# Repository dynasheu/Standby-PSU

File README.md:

# Standby-PSU
Small sandby PSU for low power applications.

## standby-psu-test
This sketch is for debugging and testing on arduino. Uses normal IRremote.h library.

## standby-psu-master
This sketch is for use with ATTiny.
Uses tiny_IRremote.h and SendOnlySoftwareSerial.h libraries.

I/O:
- button
- led
- relay
- ir
- serial out

PCB and components coming soon

## standby-psu-slave
Comming soon.

This sketch is for use with ATTiny.
Uses ReceiveOnlySoftwareSerial.h library.

I/O:
- button
- led
- relay
- mute relay
- serial in

Same PCB as master.

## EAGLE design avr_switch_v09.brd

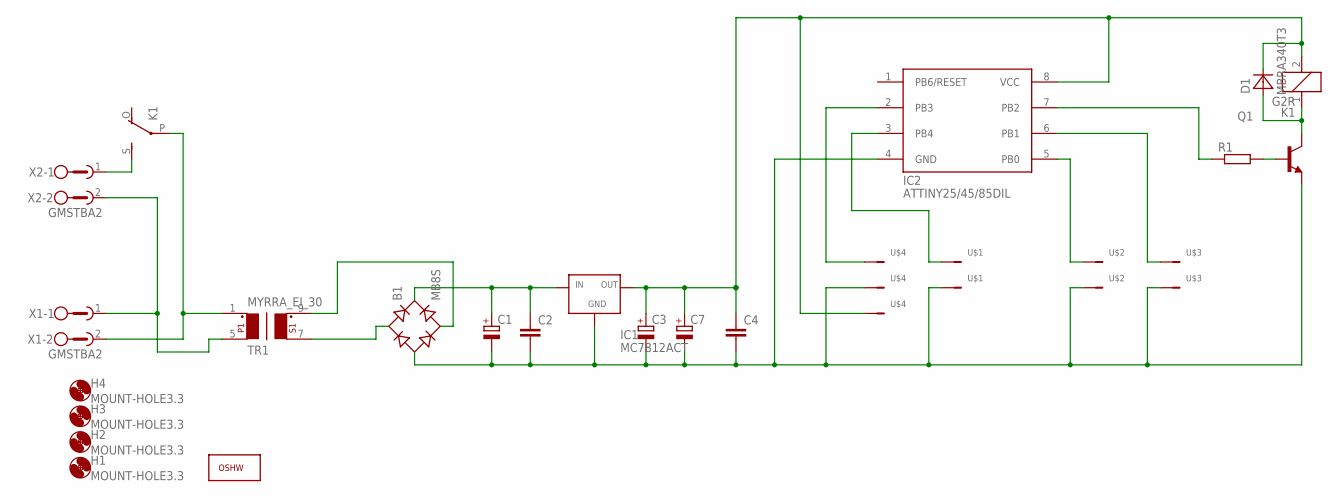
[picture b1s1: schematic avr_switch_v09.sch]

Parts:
B1: MB8S; SOIC-4
C1: CPOL-EUE5-10.5; E5-10,5
C2, C4: C-EUC0805; C0805
C3: CPOL-EUCT6032; CT6032
C7: CPOL-EUD/7343-31W; D/7343-31W
D1: MBRA340T3; SMA
H1, H2, H3, H4: MOUNT-HOLE3.3; 3,3
IC1: MC7812ACT; TO220V
IC2: ATTINY25/45/85DIL; DIL08
K1: G2R
Q1: BC548-NPN-TO92-CBE; TO92-CBE
R1: R-EU_R1206; R1206
TR1: MYRRA_EI_30; MYRRA-EI30
U$1, U$2, U$3: MOLEX-VERT-KK-2-; MOLEX-KK-VERT-2PIN
U$4: MOLEX-VERT-KK-3-3PIN; MOLEX-KK-VERT-3PIN
U$5: OSHWOSHW_TOP; OSHW_F
X1, X2: GMSTBA2

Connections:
GND: B1.-, C1.-, C2.2, C3.-, C4.2, C7.-, IC1.2 (GND), IC2.4 (GND), Q1.E, U$1.1, U$2.1, U$3.1, U$4.2
unnamed: IC2.7 (PB2), R1.1
unnamed: B1.~1 (AC1), TR1.7
unnamed: B1.~2 (AC2), TR1.9
unnamed: IC2.3 (PB4), U$1.2
unnamed: IC2.5 (PB0), U$2.2
unnamed: IC2.6 (PB1), U$3.2
unnamed: Q1.B, R1.2
unnamed: K1.S, X2.1
unnamed: B1.+, C1.+, C2.1, IC1.1 (IN)
unnamed: TR1.5, X1.1, X2.2
unnamed: K1.P, TR1.1, X1.2
unnamed: IC2.2 (PB3), U$4.3
RELN: D1.A, K1.1, Q1.C
VCC: C3.+, C4.1, C7.+, D1.C, IC1.3 (OUT), IC2.8 (VCC), K1.2, U$4.1

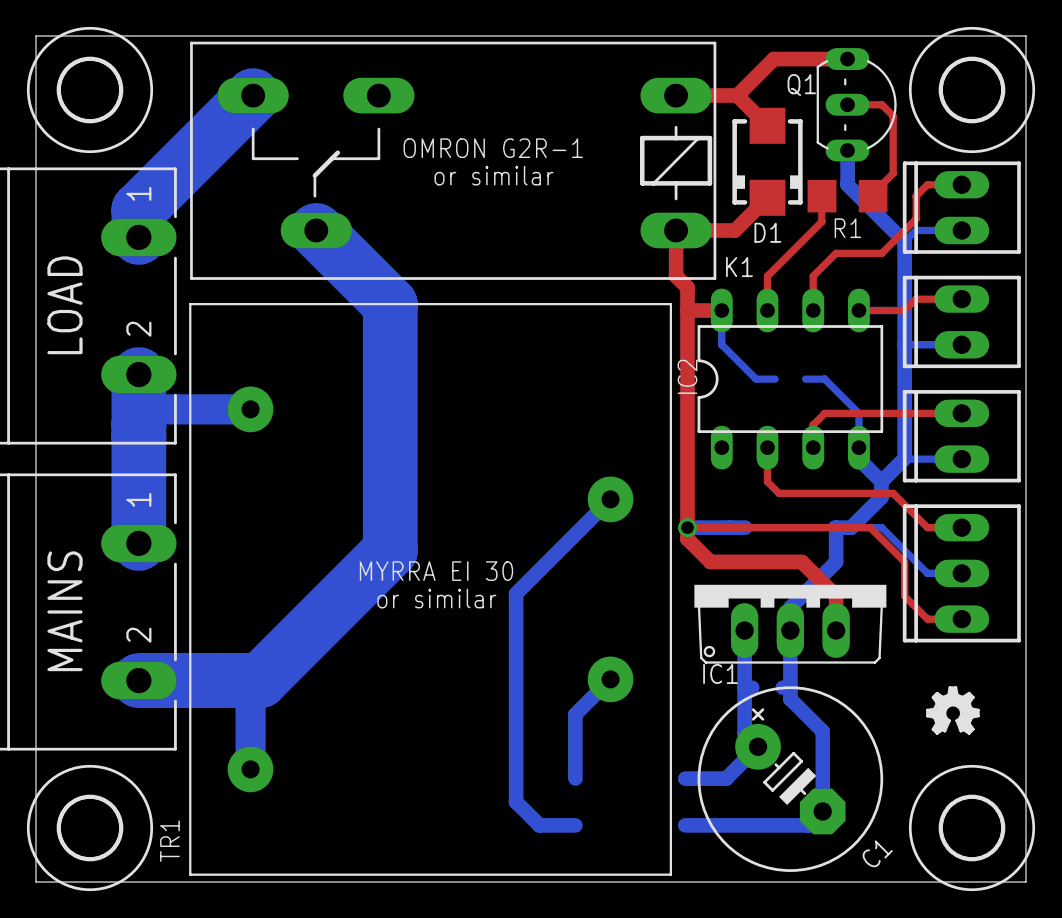
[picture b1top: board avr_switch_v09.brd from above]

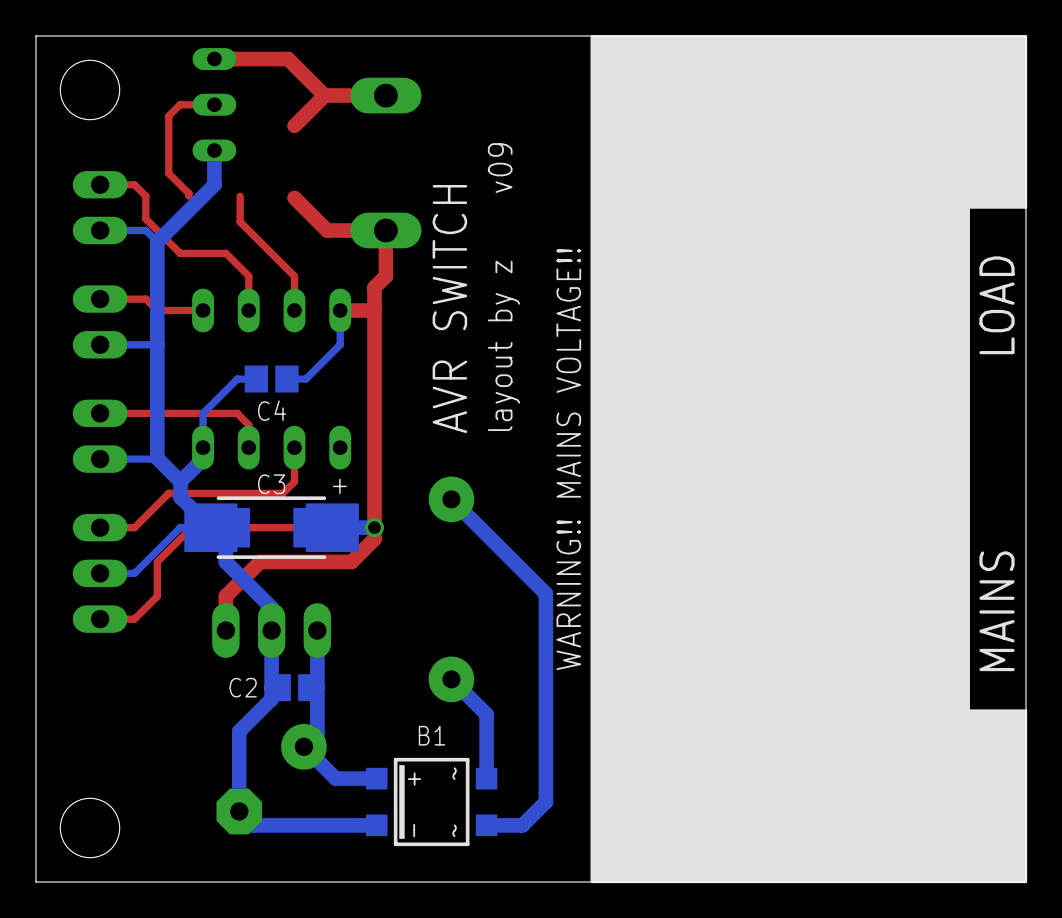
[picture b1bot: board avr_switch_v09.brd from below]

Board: 2 copper layers, 55.0 x 47.0 mm, 24 parts (5 on the bottom side), 15 nets.

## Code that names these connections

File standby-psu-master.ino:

//load libraries
#include "IRremote.h"
#include "SendOnlySoftwareSerial.h"

//pinout
#define relayPin PB2
#define ledPin PB1
#define buttonPin PB0
#define serialOutPin PB4
#define irPin PB3

int ledState = HIGH;        // state of standby led. turned HIGH when system is off
int powerState = LOW;       // power state, LOW when system is off

unsigned long powerStateTimer = 0;               // time snapshot when power state changed
long powerStateDelay = 15000;                    // power state delay time

// IR setup
IRrecv irrecv(irPin);
decode_results results;

// Software serial
SendOnlySoftwareSerial mySerial (serialOutPin);       // Tx pin

void setup() {
    //serial setup
    mySerial.begin(9600);

    //pinout setup
    pinMode(buttonPin, INPUT_PULLUP);
    pinMode(ledPin, OUTPUT);
    pinMode(irPin, INPUT);
    pinMode(relayPin, OUTPUT);

    //defaults
    digitalWrite(ledPin, LED_State);
    digitalWrite(relayPin, powerState);

    //ir setup
    irrecv.enableIRIn();
}

void loop() {
    //startup delay and powerdown blinking led delay
    while (millis() - powerStateTimer < powerStateDelay) {
        digitalWrite(ledPin, HIGH);
        delay(50);
        digitalWrite(ledPin, LOW);
        delay(950);
    }
    //reset led to correct state
    digitalWrite(ledPin, ledState);

    //read button
    //read ir
    //set relay
    //send serial data
}

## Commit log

2018-01-30 Test prototypes of Standby PSU
    Not for actual use.
2018-01-30 Rename avr_switch_v09.brd to prototype/avr_switch_v09.brd
2018-01-30 Rename avr_switch_v09.sch to prototype/avr_switch_v09.sch
2018-09-02 sketch created
2018-09-02 test
2018-09-02 initial setup done
2018-09-08 added test sketch for testing on arduino
2018-09-08 button and relay portion working
2018-09-08 fixed issue with short press on turn on
2018-09-08 cleared the code a bit and added ir codes for xbox one media remote
2018-09-08 kinda finished still need to debug
2018-09-08 addes serial codes
2018-09-08 added description
2018-09-08 typo
2018-09-08 description edit
2018-09-08 added slave folder and file
2018-09-08 added master sketch from test
2018-09-08 fixed description
2018-09-08 pin descriptions
